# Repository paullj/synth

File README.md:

# Synth

<!-- TODO: Rename to something cooler -->

> **Note**: This project is still in its early stages and is not ready for use. ie it doesn't do anything yet and this repo is fairly empty.

This repo is a monorepo composed of multiple projects that are used to make a synthesizer. The aim of the project is to learn embedded, lower level programming with Rust, and electronic engineering. It is very much a work in progress, I have no idea what I'm doing.

I am going to start with just a simple MIDI controller and see how that goes first. Eventually I would like to make a full groove box with a sequencer and a bunch of other stuff but that is a long way off.

- [`synth-firmware`](https://github.com/paullj/synth/blob/main/synth-firmware/README.md): Firmware for custom board that sends MIDI messages over USB
- [`synth-hardware`](https://github.com/paullj/synth/blob/main/synth-hardware/README.md): Hardware design files for the MIDI keyboard

## Development

This project uses [just](https://github.com/casey/just) as a task runner. Once installed run `just` in the repo root to see the available tasks. You will also need to install [Rust](https://www.rust-lang.org/tools/install) and a few other dependencies, you can run `just check-setup` to check if you have everything installed.

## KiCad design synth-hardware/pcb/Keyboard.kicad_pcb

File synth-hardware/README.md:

# synth-hardware

This folder contains the hardware design files for the MIDI keyboard. There are a number of components that are in this directory:

- `pcb`: The PCB schematic and layout design files for the MIDI keyboard.
- `case`: The CAD files for the case of the MIDI keyboard.

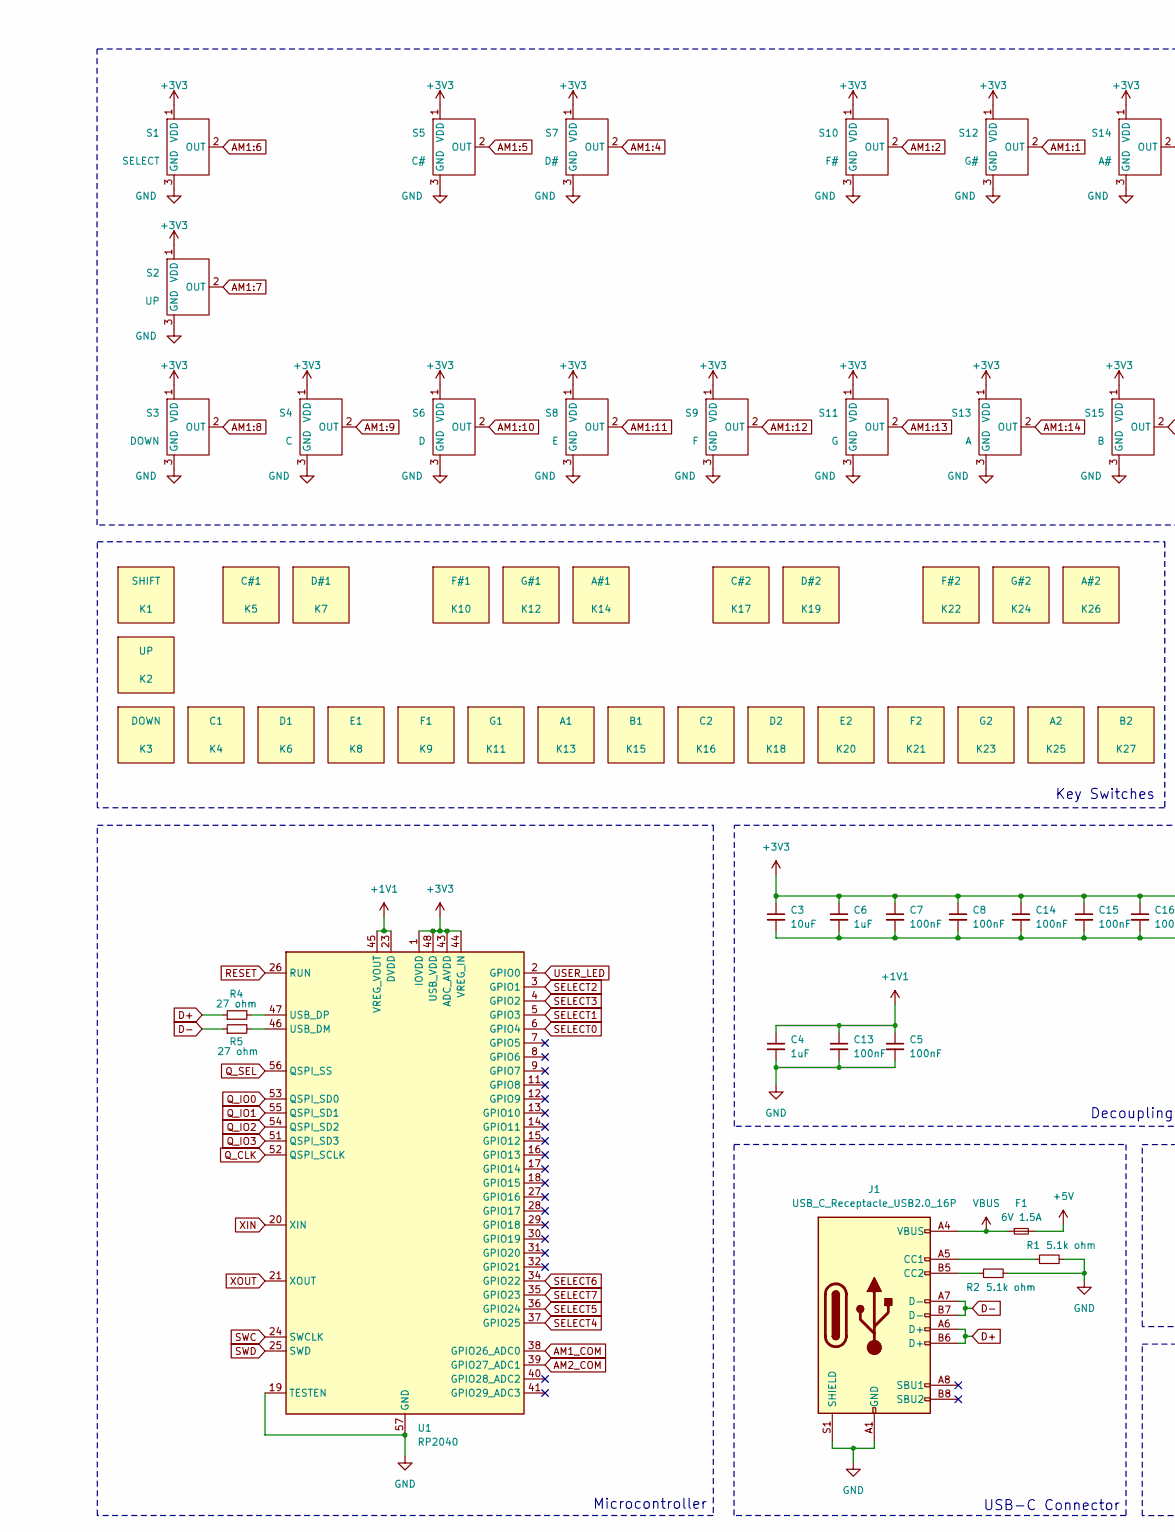
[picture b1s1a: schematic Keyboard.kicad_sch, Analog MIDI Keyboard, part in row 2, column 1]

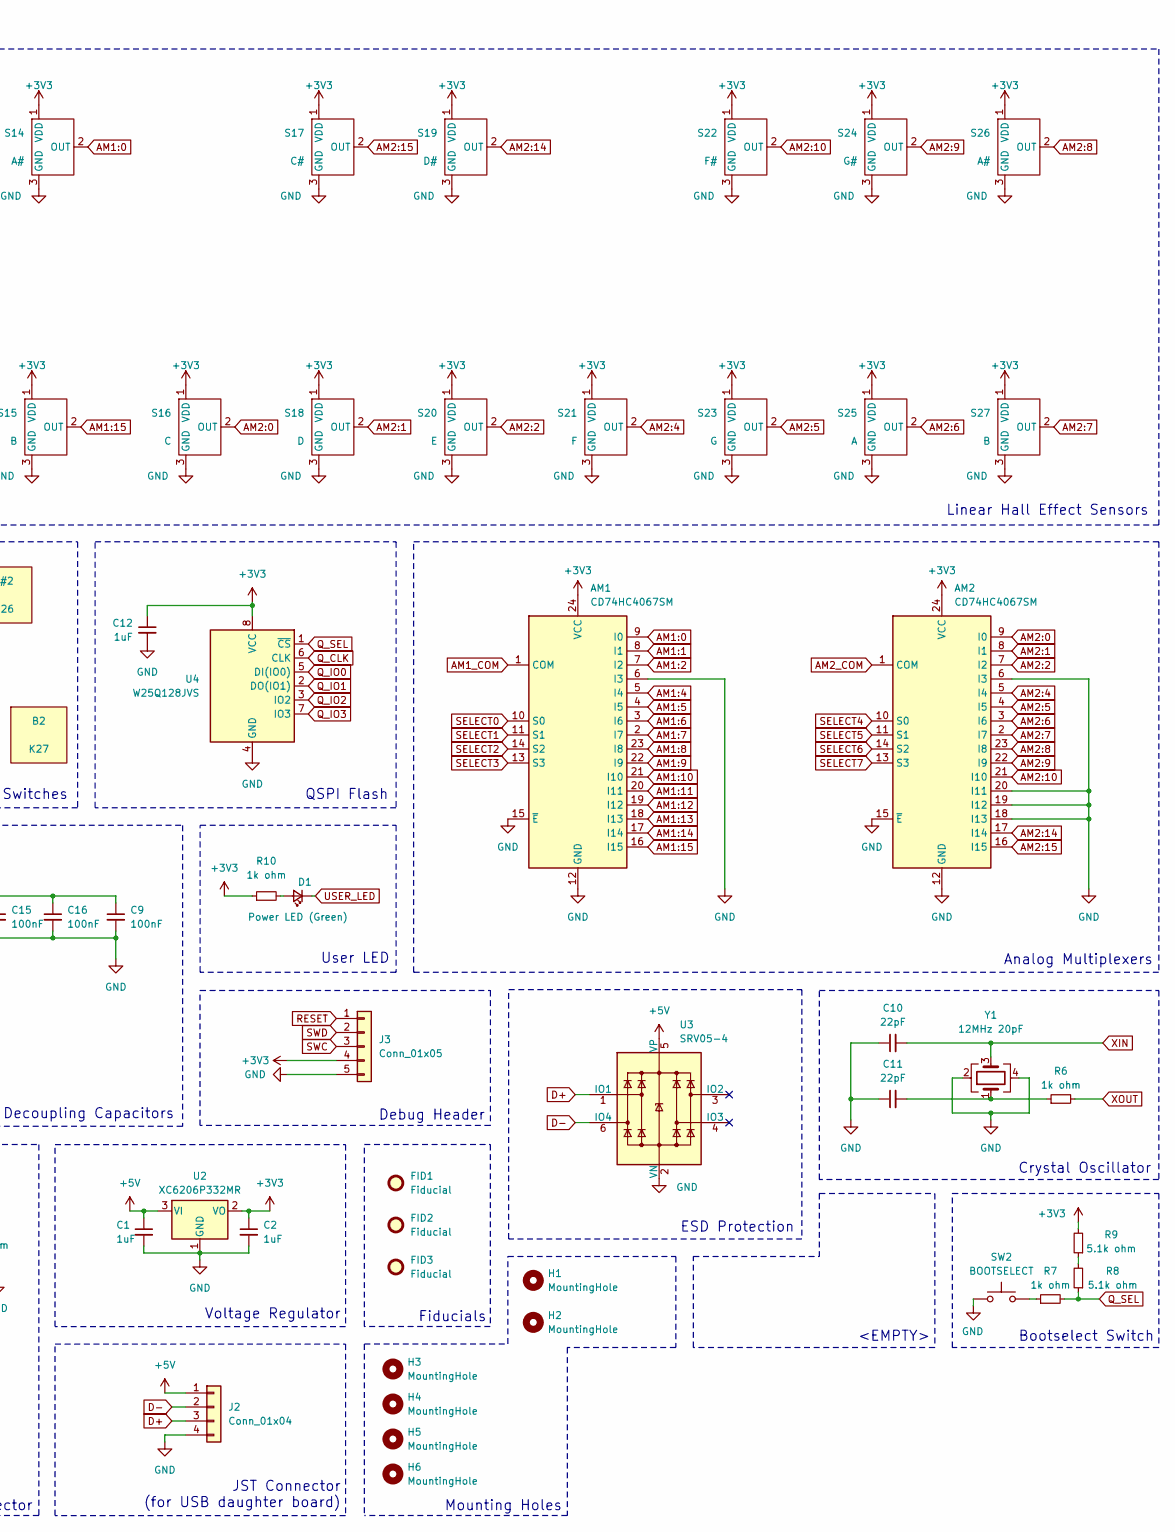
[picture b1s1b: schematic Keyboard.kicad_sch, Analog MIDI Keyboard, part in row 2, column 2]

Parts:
AM1, AM2: CD74HC4067SM; SSOP-24_5.3x8.2mm_P0.65mm; LCSC C98457
C1, C2, C4, C6, C12: 1uF; C_0402_1005Metric; LCSC C52923
C3: 10uF; C_0603_1608Metric; LCSC C96446
C5, C7, C8, C9, C13, C14, C15, C16: 100nF; C_0402_1005Metric; LCSC C307331
C10, C11: 22pF; C_0402_1005Metric; LCSC C1555
D1: Power LED (Green); LED_0805_2012Metric; LCSC C2297
F1: 6V 1.5A; Fuse_1206_3216Metric; LCSC C2838983
FID1, FID2, FID3: Fiducial; Fiducial_1mm_Mask2mm
H1, H2, H3, H4, H5, H6: MountingHole; MountingHole_2.2mm_M2_DIN965_Pad
J1: USB_C_Receptacle_USB2.0_16P; USB_C_Receptacle_HRO_TYPE-C-31-M-12; LCSC C165948
J2: Conn_01x04; JST_SH_SM04B-SRSS-TB_1x04-1MP_P1.00mm_Horizontal
J3: Conn_01x05; PinHeader_1x05_P2.54mm_Vertical
K1: SHIFT; Generic_MX_PCB_1u
K2: UP; Generic_MX_PCB_1u
K3: DOWN; Generic_MX_PCB_1u
K4: C1; Generic_MX_PCB_2u
K5: C#1; Generic_MX_PCB_1u
K6: D1; Generic_MX_PCB_2u
K7: D#1; Generic_MX_PCB_1u
K8: E1; Generic_MX_PCB_2u
K9: F1; Generic_MX_PCB_2u
K10: F#1; Generic_MX_PCB_1u
K11: G1; Generic_MX_PCB_2u
K12: G#1; Generic_MX_PCB_1u
K13: A1; Generic_MX_PCB_2u
K14: A#1; Generic_MX_PCB_1u
K15: B1; Generic_MX_PCB_2u
K16: C2; Generic_MX_PCB_2u
K17: C#2; Generic_MX_PCB_1u
K18: D2; Generic_MX_PCB_2u
K19: D#2; Generic_MX_PCB_1u
K20: E2; Generic_MX_PCB_2u
K21: F2; Generic_MX_PCB_2u
K22: F#2; Generic_MX_PCB_1u
K23: G2; Generic_MX_PCB_2u
K24: G#2; Generic_MX_PCB_1u
K25: A2; Generic_MX_PCB_2u
K26: A#2; Generic_MX_PCB_1u
K27: B2; Generic_MX_PCB_2u
R1, R2, R8, R9: 5.1k ohm; R_0402_1005Metric; LCSC C25905
R4, R5: 27 ohm; R_0603_1608Metric; LCSC C25190
R6, R7, R10: 1k ohm; R_0402_1005Metric; LCSC C11702
S1: SELECT; SOT-23-3; MPN GH39FKSW; LCSC C266230
S2: UP; SOT-23-3; MPN GH39FKSW; LCSC C266230
S3: DOWN; SOT-23-3; MPN GH39FKSW; LCSC C266230
S4, S16: C; SOT-23-3; MPN GH39FKSW; LCSC C266230
S5, S17: C#; SOT-23-3; MPN GH39FKSW; LCSC C266230
S6, S18: D; SOT-23-3; MPN GH39FKSW; LCSC C266230
S7, S19: D#; SOT-23-3; MPN GH39FKSW; LCSC C266230
S8, S20: E; SOT-23-3; MPN GH39FKSW; LCSC C266230
S9, S21: F; SOT-23-3; MPN GH39FKSW; LCSC C266230
S10, S22: F#; SOT-23-3; MPN GH39FKSW; LCSC C266230
S11, S23: G; SOT-23-3; MPN GH39FKSW; LCSC C266230
S12, S24: G#; SOT-23-3; MPN GH39FKSW; LCSC C266230
S13, S25: A; SOT-23-3; MPN GH39FKSW; LCSC C266230
S14, S26: A#; SOT-23-3; MPN GH39FKSW; LCSC C266230
S15, S27: B; SOT-23-3; MPN GH39FKSW; LCSC C266230
SW2: BOOTSELECT; SW_SPST_TL3342; LCSC C318884
U1: RP2040; QFN-56-1EP_7x7mm_P0.4mm_EP3.2x3.2mm; LCSC C2040
U2: XC6206P332MR; SOT-23; LCSC C5148692
U3: SRV05-4; SOT-23-6-routable; LCSC C558418
U4: W25Q128JVS; SOIC-8_5.23x5.23mm_P1.27mm; LCSC C97521
Y1: 12MHz 20pF; Crystal_SMD_3225-4Pin_3.2x2.5mm; LCSC C9002

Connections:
+1V1: C4.1, C5.1, C13.1, U1.23 (DVDD), U1.45 (VREG_VOUT), U1.50 (DVDD)
+3V3: AM1.24 (VCC), AM2.24 (VCC), C2.1, C3.1, C6.1, C7.1, C8.1, C9.1, C12.1, C14.1, C15.1, C16.1, J3.4, R9.2, R10.1, S1.1 (VDD), S2.1 (VDD), S3.1 (VDD), S4.1 (VDD), S5.1 (VDD), S6.1 (VDD), S7.1 (VDD), S8.1 (VDD), S9.1 (VDD), S10.1 (VDD), S11.1 (VDD), S12.1 (VDD), S13.1 (VDD), S14.1 (VDD), S15.1 (VDD), S16.1 (VDD), S17.1 (VDD), S18.1 (VDD), S19.1 (VDD), S20.1 (VDD), S21.1 (VDD), S22.1 (VDD), S23.1 (VDD), S24.1 (VDD), S25.1 (VDD), S26.1 (VDD), S27.1 (VDD), U1.1 (IOVDD), U1.10 (IOVDD), U1.22 (IOVDD), U1.33 (IOVDD), U1.42 (IOVDD), U1.43 (ADC_AVDD), U1.44 (VREG_IN), U1.48 (USB_VDD), U1.49 (IOVDD), U2.2 (VO), U4.8 (VCC)
+5V: C1.1, F1.2, J2.1, U2.3 (VI), U3.5 (VP)
AM1:0: AM1.9 (I0), S14.2 (OUT)
AM1:1: AM1.8 (I1), S12.2 (OUT)
AM1:2: AM1.7 (I2), S10.2 (OUT)
AM1:4: AM1.5 (I4), S7.2 (OUT)
AM1:5: AM1.4 (I5), S5.2 (OUT)
AM1:6: AM1.3 (I6), S1.2 (OUT)
AM1:7: AM1.2 (I7), S2.2 (OUT)
AM1:8: AM1.23 (I8), S3.2 (OUT)
AM1:9: AM1.22 (I9), S4.2 (OUT)
AM1:10: AM1.21 (I10), S6.2 (OUT)
AM1:11: AM1.20 (I11), S8.2 (OUT)
AM1:12: AM1.19 (I12), S9.2 (OUT)
AM1:13: AM1.18 (I13), S11.2 (OUT)
AM1:14: AM1.17 (I14), S13.2 (OUT)
AM1:15: AM1.16 (I15), S15.2 (OUT)
AM1_COM: AM1.1 (COM), U1.38 (GPIO26_ADC0)
AM2:0: AM2.9 (I0), S16.2 (OUT)
AM2:1: AM2.8 (I1), S18.2 (OUT)
AM2:2: AM2.7 (I2), S20.2 (OUT)
AM2:4: AM2.5 (I4), S21.2 (OUT)
AM2:5: AM2.4 (I5), S23.2 (OUT)
AM2:6: AM2.3 (I6), S25.2 (OUT)
AM2:7: AM2.2 (I7), S27.2 (OUT)
AM2:8: AM2.23 (I8), S26.2 (OUT)
AM2:9: AM2.22 (I9), S24.2 (OUT)
AM2:10: AM2.21 (I10), S22.2 (OUT)
AM2:14: AM2.17 (I14), S19.2 (OUT)
AM2:15: AM2.16 (I15), S17.2 (OUT)
AM2_COM: AM2.1 (COM), U1.39 (GPIO27_ADC1)
D+: J1.A6 (D+), J1.B6 (D+), J2.3, R4.1, U3.1 (IO1)
D-: J1.A7 (D-), J1.B7 (D-), J2.2, R5.1, U3.6 (IO4)
GND: AM1.6 (I3), AM1.12 (GND), AM1.15 (~E), AM2.6 (I3), AM2.12 (GND), AM2.15 (~E), AM2.18 (I13), AM2.19 (I12), AM2.20 (I11), C1.2, C2.2, C3.2, C4.2, C5.2, C6.2, C7.2, C8.2, C9.2, C10.1, C11.1, C12.2, C13.2, C14.2, C15.2, C16.2, J1.A1 (GND), J1.A12 (GND), J1.B1 (GND), J1.B12 (GND), J1.S1 (SHIELD), J2.4, J3.5, R1.2, R2.2, S1.3 (GND), S2.3 (GND), S3.3 (GND), S4.3 (GND), S5.3 (GND), S6.3 (GND), S7.3 (GND), S8.3 (GND), S9.3 (GND), S10.3 (GND), S11.3 (GND), S12.3 (GND), S13.3 (GND), S14.3 (GND), S15.3 (GND), S16.3 (GND), S17.3 (GND), S18.3 (GND), S19.3 (GND), S20.3 (GND), S21.3 (GND), S22.3 (GND), S23.3 (GND), S24.3 (GND), S25.3 (GND), S26.3 (GND), S27.3 (GND), SW2.1, U1.19 (TESTEN), U1.57 (GND), U2.1 (GND), U3.2 (VN), U4.4 (GND), Y1.2, Y1.4
unnamed: C11.2, R6.1, Y1.1
unnamed: D1.2 (A), R10.2
unnamed: J1.A5 (CC1), R1.1
unnamed: J1.B5 (CC2), R2.1
unnamed: R7.1, SW2.2
unnamed: R8.2, R9.1
unnamed: R5.2, U1.46 (USB_DM)
unnamed: R4.2, U1.47 (USB_DP)
Q_CLK: U1.52 (QSPI_SCLK), U4.6 (CLK)
Q_IO0: U1.53 (QSPI_SD0), U4.5 (DI(IO0))
Q_IO1: U1.55 (QSPI_SD1), U4.2 (DO(IO1))
Q_IO2: U1.54 (QSPI_SD2), U4.3 (IO2)
Q_IO3: U1.51 (QSPI_SD3), U4.7 (IO3)
Q_SEL: R7.2, R8.1, U1.56 (QSPI_SS), U4.1 (~CS)
RESET: J3.1, U1.26 (RUN)
SELECT0: AM1.10 (S0), U1.6 (GPIO4)
SELECT1: AM1.11 (S1), U1.5 (GPIO3)
SELECT2: AM1.14 (S2), U1.3 (GPIO1)
SELECT3: AM1.13 (S3), U1.4 (GPIO2)
SELECT4: AM2.10 (S0), U1.37 (GPIO25)
SELECT5: AM2.11 (S1), U1.36 (GPIO24)
SELECT6: AM2.14 (S2), U1.34 (GPIO22)
SELECT7: AM2.13 (S3), U1.35 (GPIO23)
SWC: J3.3, U1.24 (SWCLK)
SWD: J3.2, U1.25 (SWD)
USER_LED: D1.1 (K), U1.2 (GPIO0)
VBUS: F1.1, J1.A4 (VBUS), J1.A9 (VBUS), J1.B4 (VBUS), J1.B9 (VBUS)
XIN: C10.2, U1.20 (XIN), Y1.3
XOUT: R6.2, U1.21 (XOUT)

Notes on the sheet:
Debug Header
Decoupling Capacitors
Microcontroller
Bootselect Switch
Voltage Regulator
Fiducials
QSPI Flash
<EMPTY>
Crystal Oscillator
JST Connector (for USB daughter board)
Key Switches
USB-C Connector
ESD Protection
Mounting Holes
User LED
Analog Multiplexers
Linear Hall Effect Sensors

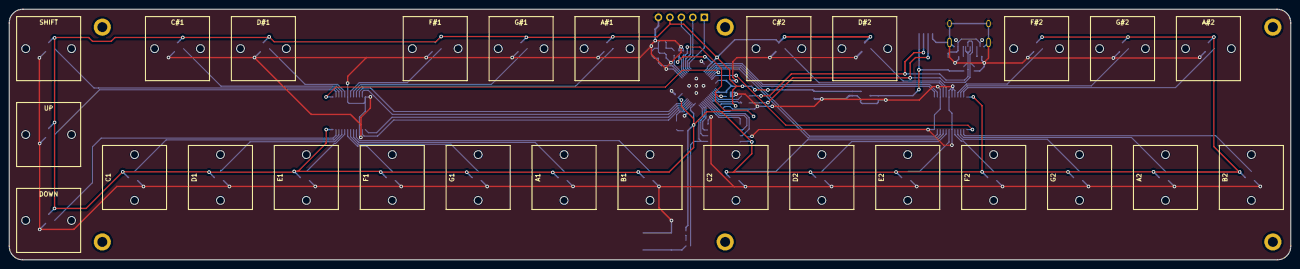
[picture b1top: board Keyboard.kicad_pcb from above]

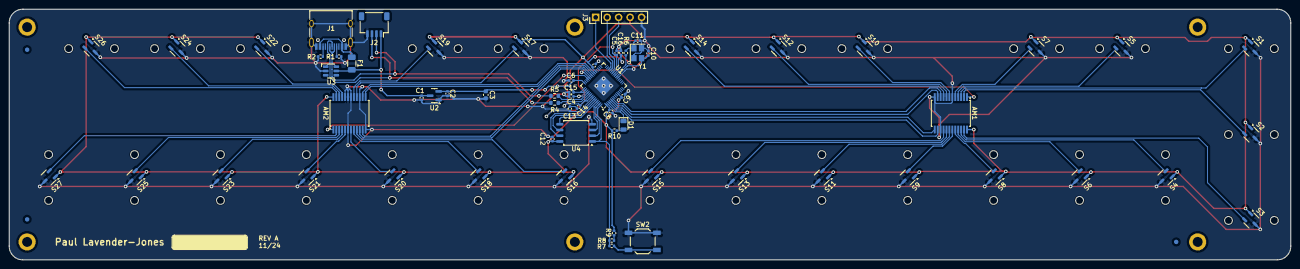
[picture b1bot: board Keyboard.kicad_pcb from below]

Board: 2 copper layers, 284.2 x 55.6 mm, 101 parts (68 on the bottom side), 64 nets.

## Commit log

2024-01-02 init
2024-01-02 fix: state machine call
2024-01-02 chore: setup workspace
2024-01-03 feat: add `just`, add minimal firmware remove cargo workspace
2024-01-03 chore: rm Cargo.lock, update readme
2024-01-04 chore: rename packages with _
2024-01-04 fix: rename
2024-01-04 chore: seperate gitignore
2024-01-04 chore: add editorconfig
2024-01-05 fix: wrongly named config.toml
2024-01-07 feat(firmware): add basic midi usb in/out
2024-01-07 feat(firmware): add basic midi usb in/out (#1)
    * chore: seperate gitignore
    * chore: add editorconfig
    * fix: wrongly named config.toml
    * feat(firmware): add basic midi usb in/out
    ---------
2024-01-17 chore: move examples
2024-01-17 chore: remove rs from editorconfig and justfile changes
2024-01-17 feat(app): add basic midi in/out and cross compilation
2024-01-20 chore(docs): add design whiteboard
2024-01-20 feat(app): basic polyphonic synth
2024-01-20 feat(app): most basic synth (#2)
    * chore: seperate gitignore
    * chore: add editorconfig
    * fix: wrongly named config.toml
    * feat(firmware): add basic midi usb in/out
    * chore: move examples
    * chore: remove rs from editorconfig and justfile changes
2024-01-22 chore: rm unused example
2024-01-22 chore: appease rust analyzer
2024-01-22 feat(app): adsr + simple shared params
2024-01-22 feat(app): adsr (#3)
    * chore: seperate gitignore
    * chore: add editorconfig
    * fix: wrongly named config.toml
    * feat(firmware): add basic midi usb in/out
    * chore: move examples
    * chore: remove rs from editorconfig and justfile changes
2024-01-25 chore(docs): add todo and mock ui
2024-01-25 feat(app): add state machine and separate actions and engine midi messages
2024-01-25 feat(app): state machine and better midi messages (#4)
    * chore: seperate gitignore
    * chore: add editorconfig
    * fix: wrongly named config.toml
    * feat(firmware): add basic midi usb in/out
    * chore: move examples
    * chore: remove rs from editorconfig and justfile changes
2024-01-28 Add adsr screen vis and live control
2024-01-30 feat: minor changes to adsr vis
2024-01-30 feat(app): adsr screen and live changes to engine (#5)
    * chore: seperate gitignore
    * chore: add editorconfig
    * fix: wrongly named config.toml
    * feat(firmware): add basic midi usb in/out
    * chore: move examples
    * chore: remove rs from editorconfig and justfile changes
2024-09-04 feat(app): get real build working on hardware
2024-09-04 chore(app): add env example
2024-09-10 feat: local+pi setup, systemd service
2024-09-15 feat(firmware): add basic encoder tests
2024-10-09 feat(hardware): initial commit of keyboard pcb design
2024-10-21 feat(hardware): first revision pcb
2024-11-12 feat(hardware): fix usb and add more components
2024-11-12 feat(hardware): finished adding lcsc for all components
2024-11-29 feat(hardware): kicad kibot workflow
2024-11-29 fix(hardware): update workflow
2024-11-29 chore(hardware): update workflow
2024-11-29 chore(hardware): add kibot config
2024-11-29 chore(hardware): typo
2024-11-29 fix(hardware): update build
2024-12-16 chore: update hardware actions
2024-12-30 feat: dump of hardware changes and firmware
2024-12-30 feat: dump of hardware changes and firmware (#8)
2024-12-30 chore: rename keyboard folder to pcb
2024-12-30 docs: update readmes
2024-12-30 docs: update
2025-02-26 chore: dump on 26-02-25
